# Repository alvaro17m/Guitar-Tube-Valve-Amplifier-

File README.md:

# Guitar-Tube-Valve-Amplifier-
Design and construction of a 50W electric guitar valve amplifier

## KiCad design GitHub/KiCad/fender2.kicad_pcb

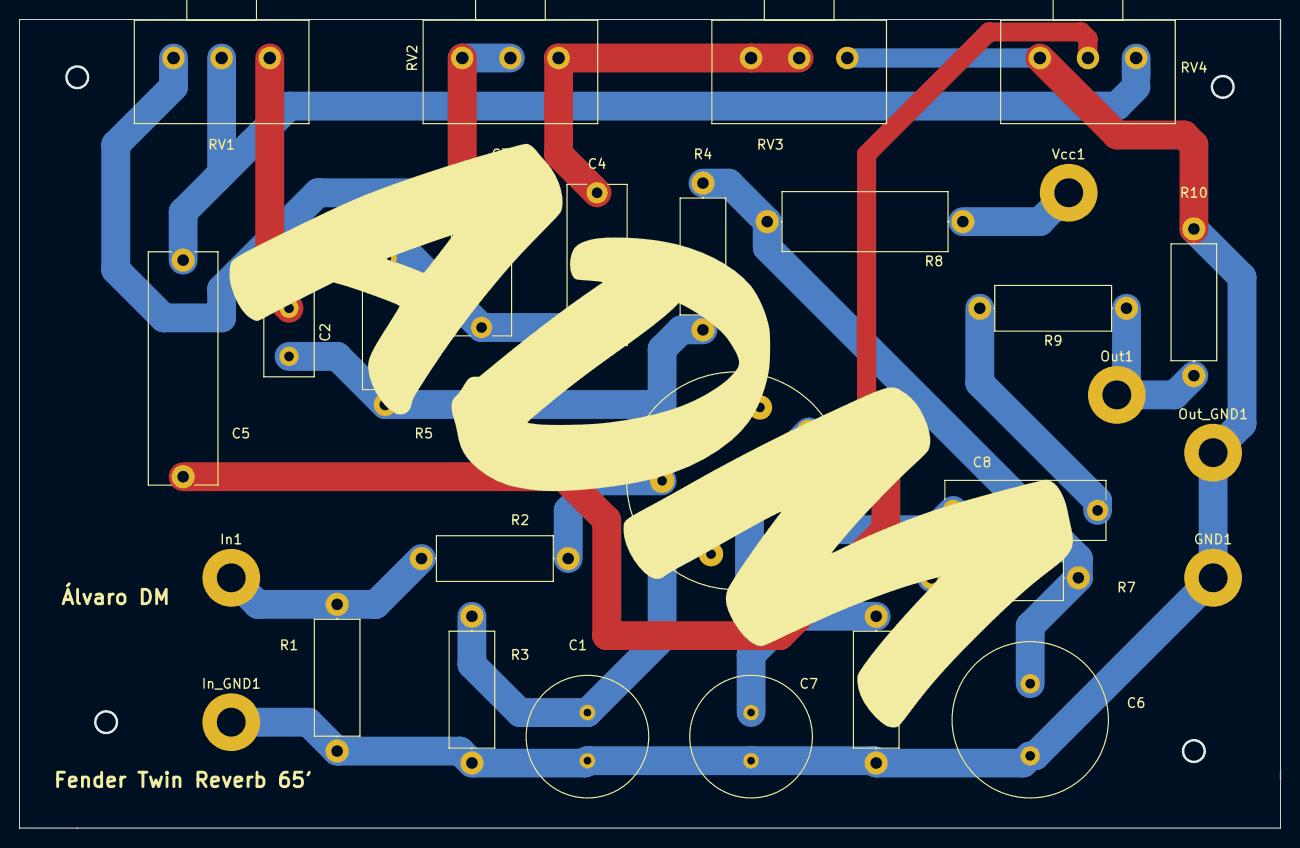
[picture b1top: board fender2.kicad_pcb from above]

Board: 2 copper layers, 131.0 x 84.0 mm, 29 parts (0 on the bottom side), 17 nets.

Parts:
C1, C7: 22uF; C_Radial_D12.5mm_H25.0mm_P5.00mm
C2: 250pF; C_Disc_D9.0mm_W5.0mm_P5.00mm
C3: 100nF; C_Rect_L16.5mm_W6.0mm_P15.00mm_MKT
C4, C8: 47nF; C_Rect_L16.5mm_W6.0mm_P15.00mm_MKT
C5: 120pF; C_Rect_L24.0mm_W7.0mm_P22.50mm_MKT
C6: 22uF; C_Radial_D16.0mm_H25.0mm_P7.50mm
GND1: GND; MountingHole_3mm_Pad
In1: In; MountingHole_3mm_Pad
In_GND1: In_GND; MountingHole_3mm_Pad
Out1: Out; MountingHole_3mm_Pad
Out_GND1: Out_GND; MountingHole_3mm_Pad
R1: 1M; R_Axial_DIN0414_L11.9mm_D4.5mm_P15.24mm_Horizontal
R2: 68k; R_Axial_DIN0414_L11.9mm_D4.5mm_P15.24mm_Horizontal
R3: 1.5k; R_Axial_DIN0414_L11.9mm_D4.5mm_P15.24mm_Horizontal
R4, R5, R7: 100k; R_Axial_DIN0414_L11.9mm_D4.5mm_P15.24mm_Horizontal
R6: 1.8k; R_Axial_DIN0414_L11.9mm_D4.5mm_P15.24mm_Horizontal
R8: 1K; R_Axial_DIN0617_L17.0mm_D6.0mm_P20.32mm_Horizontal
R9: 220k; R_Axial_DIN0414_L11.9mm_D4.5mm_P15.24mm_Horizontal
R10: 820k; R_Axial_DIN0414_L11.9mm_D4.5mm_P15.24mm_Horizontal
RV1, RV2: 250kA; Potentiometer_Alps_RK163_Single_Horizontal
RV3: 10kA; Potentiometer_Alps_RK163_Single_Horizontal
RV4: 1MA; Potentiometer_Alps_RK163_Single_Horizontal
U1: ECC83; Valve_Noval_P
Vcc1: Vcc; MountingHole_3mm_Pad

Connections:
GND: C1.2, C6.2, C7.2, GND1.1, In_GND1.1, Out_GND1.1, R1.1, R3.2, R6.2, R10.2, RV3.1, RV4.3
unnamed: C1.1, R3.1, U1.8
unnamed: C2.1, RV1.1
unnamed: C2.2, R4.2, R5.1, U1.6
unnamed: C3.1, RV1.3, RV2.2, RV2.3
unnamed: C3.2, C4.2, R5.2
unnamed: C4.1, RV2.1, RV3.2, RV3.3
unnamed: C5.1, RV1.2, RV4.1
unnamed: C5.2, RV4.2, U1.2
unnamed: C6.1, R4.1, R7.1, R8.2
unnamed: C7.1, R6.1, U1.3
unnamed: C8.1, R9.2
unnamed: C8.2, R7.2, U1.1
unnamed: In1.1, R1.2, R2.2
unnamed: Out1.1, R9.1, R10.1
unnamed: R2.1, U1.7
unnamed: R8.1, Vcc1.1

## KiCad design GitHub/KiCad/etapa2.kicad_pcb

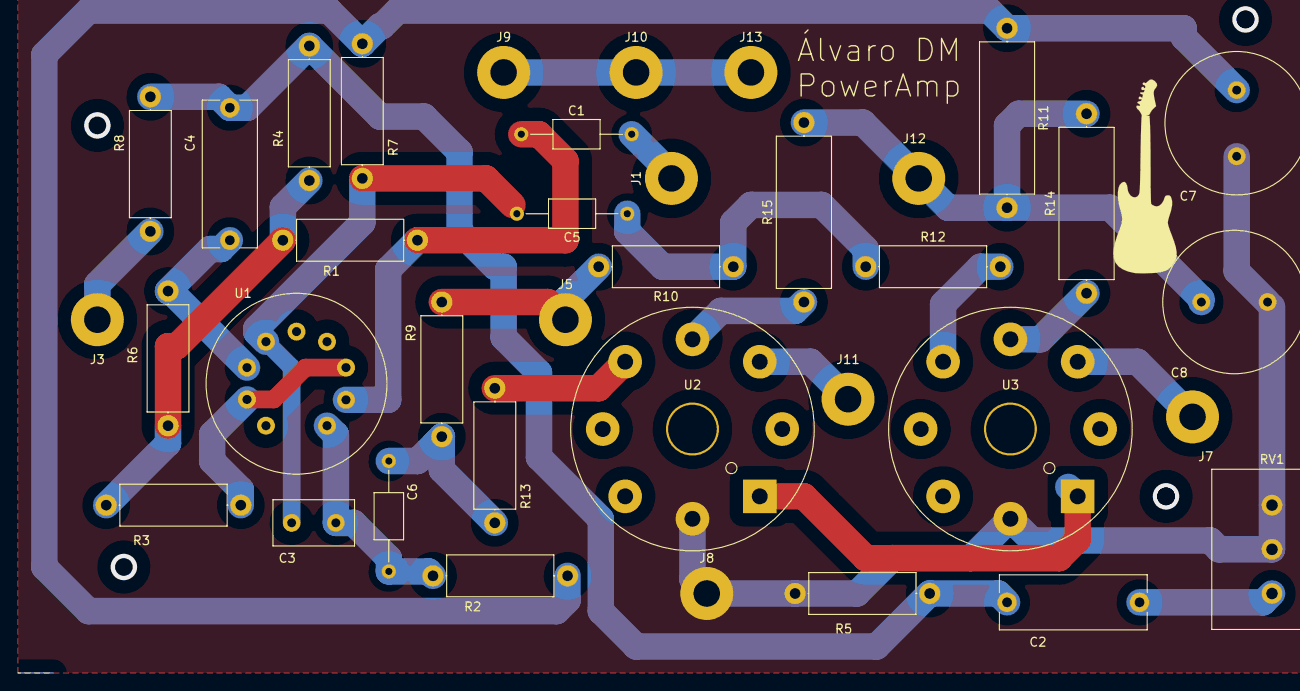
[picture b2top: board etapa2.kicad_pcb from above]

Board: 2 copper layers, 37 parts (0 on the bottom side), 24 nets.

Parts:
C1, C5, C6: 22n; C_Axial_L5.1mm_D3.1mm_P12.50mm_Horizontal
C2, C4: 100n; C_Rect_L16.5mm_W6.0mm_P15.00mm_MKT
C3: 47p; C_Disc_D9.0mm_W5.0mm_P5.00mm
C7, C8: 50uF 500V; C_Radial_D16.0mm_H25.0mm_P7.50mm
J1: In; MountingHole_3mm_Pad
J3: OT pur; MountingHole_3mm_Pad
J5: -57V; MountingHole_3mm_Pad
J7: OT Wt; MountingHole_3mm_Pad
J8: Tierra (Jack/AC); MountingHole_3mm_Pad
J9: B+; MountingHole_3mm_Pad
J10: OT bn; MountingHole_3mm_Pad
J11: OT Rd; MountingHole_3mm_Pad
J12: Choke1; MountingHole_3mm_Pad
J13: Choke2; MountingHole_3mm_Pad
R1, R6: 1M; R_Axial_DIN0414_L11.9mm_D4.5mm_P15.24mm_Horizontal
R2: 82k; R_Axial_DIN0414_L11.9mm_D4.5mm_P15.24mm_Horizontal
R3: 470R; R_Axial_DIN0414_L11.9mm_D4.5mm_P15.24mm_Horizontal
R4: 10k; R_Axial_DIN0414_L11.9mm_D4.5mm_P15.24mm_Horizontal
R5: 4k7; R_Axial_DIN0414_L11.9mm_D4.5mm_P15.24mm_Horizontal
R7, R8: 100k; R_Axial_DIN0414_L11.9mm_D4.5mm_P15.24mm_Horizontal
R9, R10: 150k; R_Axial_DIN0414_L11.9mm_D4.5mm_P15.24mm_Horizontal
R11: 10k 2W; R_Axial_DIN0617_L17.0mm_D6.0mm_P20.32mm_Horizontal
R12, R13: 5k6; R_Axial_DIN0414_L11.9mm_D4.5mm_P15.24mm_Horizontal
R14, R15: 1k 5W; R_Axial_DIN0617_L17.0mm_D6.0mm_P20.32mm_Horizontal
RV1: 22k PRESENCE; Potentiometer_Alps_RK163_Single_Horizontal
U1: ECC83; Valve_ECC-83-1
U2, U3: EL34; Valve_Octal

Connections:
GND: C7.2, C8.2, J8.1, R5.1, RV1.2, RV1.3, U2.8, U3.8
unnamed: C1.1, R1.2, U1.2
unnamed: C1.2, J1.1
unnamed: C2.1, C4.2, R4.1, R5.2, R8.2
unnamed: C2.2, RV1.1
unnamed: C3.1, C5.2, R7.1, U1.6
unnamed: C3.2, C6.2, R2.1, U1.1
unnamed: C4.1, R6.2, U1.7
unnamed: C5.1, R10.1, R12.1
unnamed: C6.1, R9.2, R13.1
unnamed: C7.1, R2.2, R7.2, R11.1
unnamed: C8.1, J12.1, R11.2, R14.2, R15.2
unnamed: J3.1, R8.1
unnamed: J5.1, R9.1, R10.2
unnamed: J7.1, U3.3
unnamed: J9.1, J10.1, J13.1
unnamed: J11.1, U2.3
unnamed: R1.1, R3.1, R4.2, R6.1
unnamed: R3.2, U1.3, U1.8
unnamed: R12.2, U3.5
unnamed: R13.2, U2.5
unnamed: R14.1, U3.4
unnamed: R15.1, U2.4
unnamed: U2.1, U3.1

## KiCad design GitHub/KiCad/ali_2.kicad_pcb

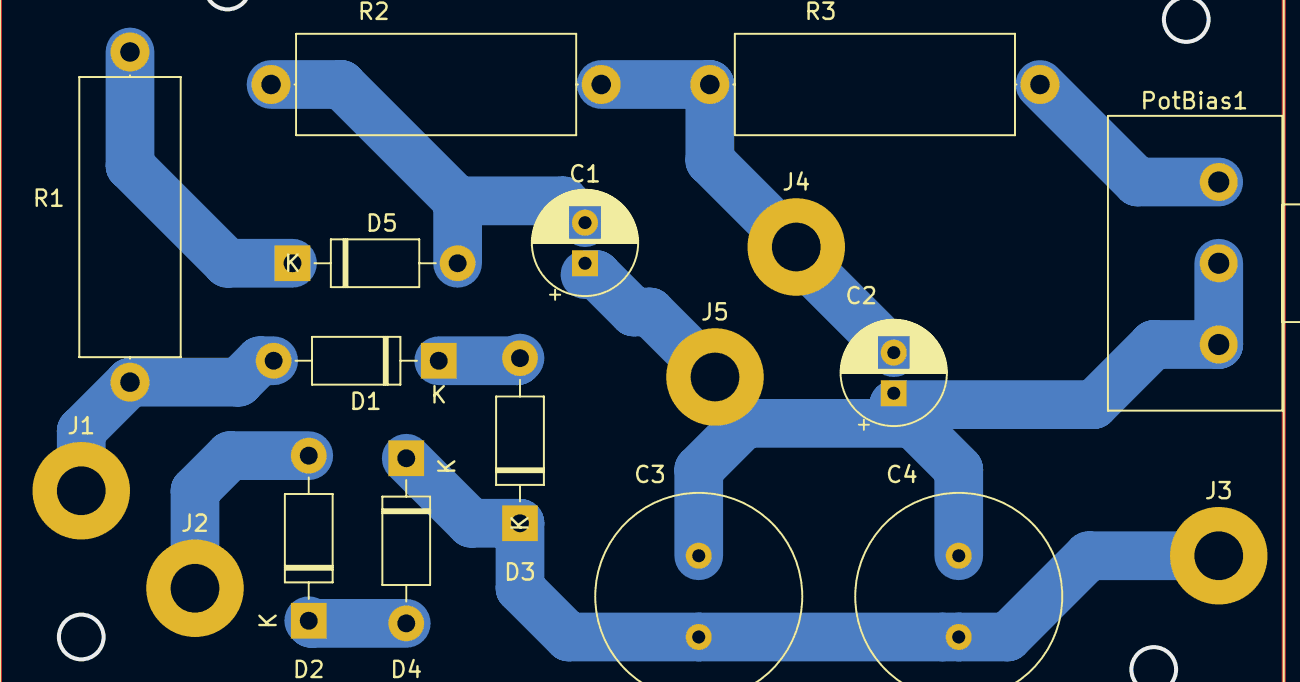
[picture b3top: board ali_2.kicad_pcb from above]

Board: 2 copper layers, 18 parts (0 on the bottom side), 10 nets.

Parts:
C1, C2: 10uF 100V; CP_Radial_D6.3mm_P2.50mm
C3, C4: 50uF 500V; C_Radial_D12.5mm_H25.0mm_P5.00mm
D1, D2, D3, D4, D5: 1N4007; D_DO-41_SOD81_P10.16mm_Horizontal
J1: Red1; MountingHole_3mm_Pad
J2: Red2; MountingHole_3mm_Pad
J3: B++ (fuse); MountingHole_3mm_Pad
J4: Neg; MountingHole_3mm_Pad
J5: Tierra; MountingHole_3mm_Pad
PotBias1: Pot 22k; Potentiometer_Alps_RK163_Single_Horizontal
R1: 120k; R_Axial_DIN0617_L17.0mm_D6.0mm_P20.32mm_Horizontal
R2: 15k; R_Axial_DIN0617_L17.0mm_D6.0mm_P20.32mm_Horizontal
R3: 47k; R_Axial_DIN0617_L17.0mm_D6.0mm_P20.32mm_Horizontal

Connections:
GND: C1.1, C2.1, C3.2, C4.2, J5.1, PotBias1.1, PotBias1.2
unnamed: C1.2, D5.2, R2.2
unnamed: C2.2, J4.1, R2.1, R3.2
unnamed: C3.1, C4.1, D3.1, D4.1, J3.1
unnamed: D1.1, D3.2
unnamed: D1.2, J1.1, R1.2
unnamed: D2.1, D4.2
unnamed: D2.2, J2.1
unnamed: D5.1, R1.1
unnamed: PotBias1.3, R3.1

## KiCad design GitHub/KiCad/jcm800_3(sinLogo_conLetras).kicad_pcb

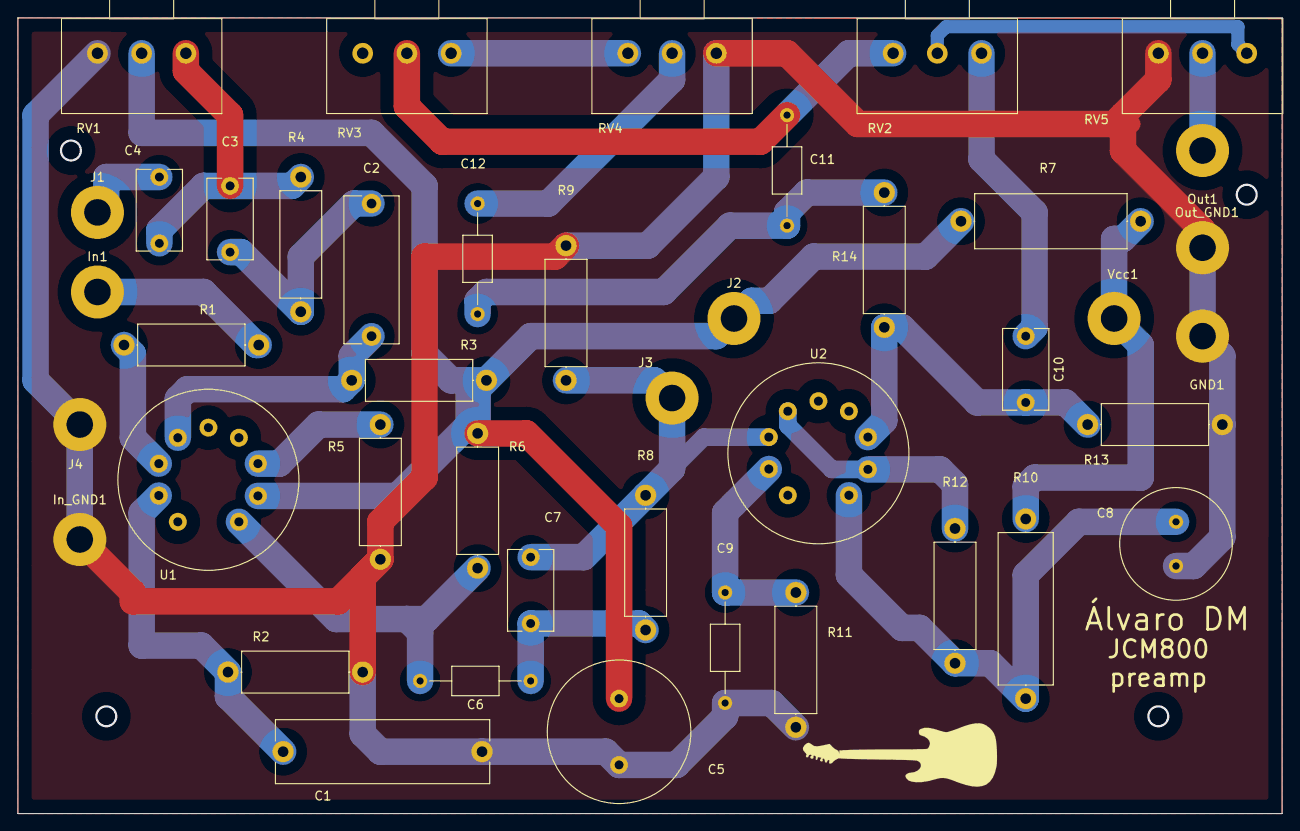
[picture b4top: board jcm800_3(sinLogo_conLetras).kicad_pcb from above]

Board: 2 copper layers, 143.0 x 90.0 mm, 43 parts (0 on the bottom side), 25 nets.

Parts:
C1: 680nF; C_Rect_L24.0mm_W7.0mm_P22.50mm_MKT
C2: 22nF; C_Rect_L16.5mm_W6.0mm_P15.00mm_MKT
C3, C7, C10: 470pF; C_Disc_D9.0mm_W5.0mm_P7.50mm
C4: 1nF; C_Disc_D9.0mm_W5.0mm_P7.50mm
C5: 47uF; C_Radial_D16.0mm_H25.0mm_P7.50mm
C6, C11, C12: 22nF; C_Axial_L5.1mm_D3.1mm_P12.50mm_Horizontal
C8: 47uF; C_Radial_D12.5mm_H25.0mm_P5.00mm
C9: 680nF; C_Axial_L5.1mm_D3.1mm_P12.50mm_Horizontal
GND1: GND; MountingHole_3mm_Pad
In1: In; MountingHole_3mm_Pad
In_GND1: In_GND; MountingHole_3mm_Pad
J1, J2, J3, J4: Conn_01x01_Female; MountingHole_3mm_Pad
Out1: Out; MountingHole_3mm_Pad
Out_GND1: Out_GND; MountingHole_3mm_Pad
R1: 68k; R_Axial_DIN0414_L11.9mm_D4.5mm_P15.24mm_Horizontal
R2: 2.7k; R_Axial_DIN0414_L11.9mm_D4.5mm_P15.24mm_Horizontal
R3, R6, R12, R13: 100k; R_Axial_DIN0414_L11.9mm_D4.5mm_P15.24mm_Horizontal
R4, R8, R9: 470k; R_Axial_DIN0414_L11.9mm_D4.5mm_P15.24mm_Horizontal
R5: 10k; R_Axial_DIN0414_L11.9mm_D4.5mm_P15.24mm_Horizontal
R7, R10: 4k7 3W; R_Axial_DIN0617_L17.0mm_D6.0mm_P20.32mm_Horizontal
R11: 820; R_Axial_DIN0414_L11.9mm_D4.5mm_P15.24mm_Horizontal
R14: 33k; R_Axial_DIN0414_L11.9mm_D4.5mm_P15.24mm_Horizontal
RV1: 1M A (Vol); Potentiometer_Alps_RK163_Single_Horizontal
RV2: 250K B (Tre); Potentiometer_Alps_RK163_Single_Horizontal
RV3: 1M A (bass); Potentiometer_Alps_RK163_Single_Horizontal
RV4: 25K B (Mid); Potentiometer_Alps_RK163_Single_Horizontal
RV5: 1M A (Level); Potentiometer_Alps_RK163_Single_Horizontal
U1, U2: ECC83; Valve_ECC-83-1
Vcc1: Vcc; MountingHole_3mm_Pad

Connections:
GND: C1.2, C5.2, C8.2, C9.2, GND1.1, In_GND1.1, J4.1, Out_GND1.1, R2.1, R5.2, R9.2, R11.2, R13.2, RV1.3, RV4.1, RV5.3
unnamed: C1.1, R2.2, U1.8
unnamed: C2.1, C3.2, R4.2
unnamed: C2.2, R3.2, U1.6
unnamed: C3.1, C4.2, R4.1, RV1.1
unnamed: C4.1, J1.1
unnamed: C5.1, J2.1, R3.1, R6.1, R7.2, RV1.2, U1.2
unnamed: C6.1, C7.2, R8.2
unnamed: C6.2, R6.2, U1.1
unnamed: C7.1, J3.1, R8.1, R9.1, U2.7
unnamed: C8.1, R10.1, R12.1, U2.1
unnamed: C9.1, R11.1, U2.8
unnamed: C10.1, RV2.1
unnamed: C10.2, R13.1, R14.1, U2.3
unnamed: C11.1, RV2.3, RV3.2
unnamed: C11.2, C12.2, R14.2
unnamed: C12.1, RV4.2
unnamed: In1.1, R1.2
unnamed: Out1.1, RV5.2
unnamed: R1.1, U1.7
unnamed: R5.1, U1.3
unnamed: R7.1, R10.2, Vcc1.1
unnamed: R12.2, U2.2, U2.6
unnamed: RV2.2, RV5.1
unnamed: RV3.1, RV4.3
